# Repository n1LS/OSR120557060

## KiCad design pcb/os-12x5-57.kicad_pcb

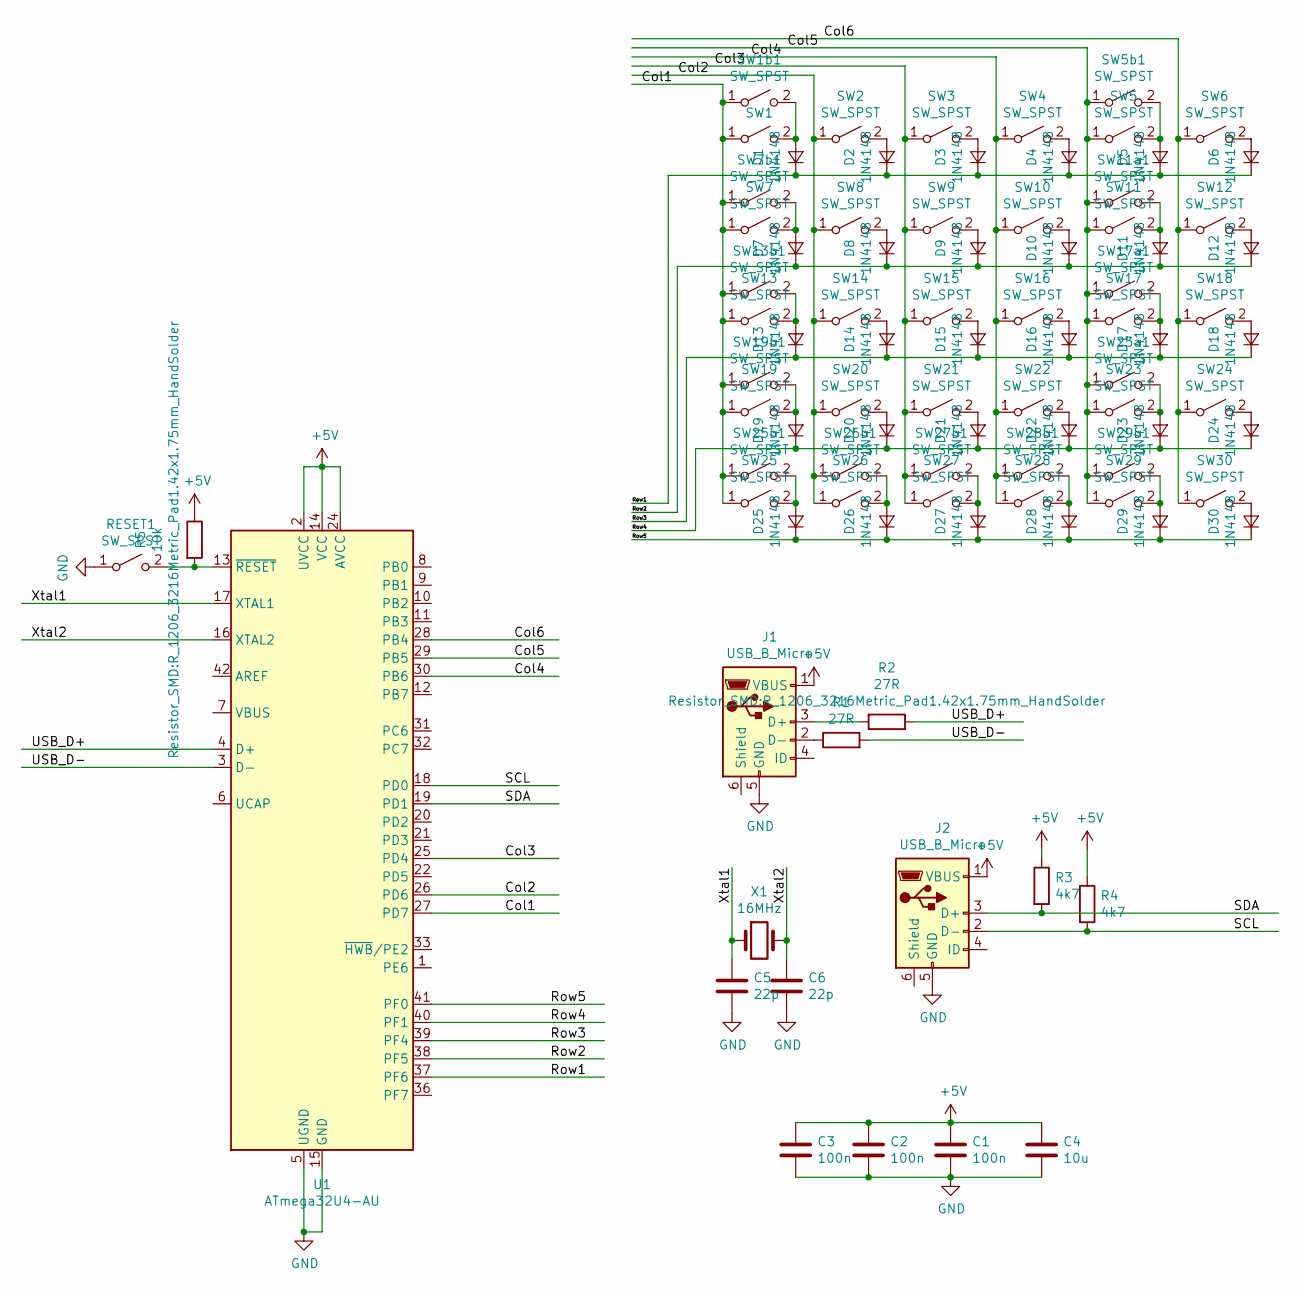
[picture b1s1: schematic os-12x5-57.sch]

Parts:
C1, C2, C3: 100n; C_1206_3216Metric_Pad1.42x1.75mm_HandSolder
C4: 10u; C_1206_3216Metric_Pad1.42x1.75mm_HandSolder
C5, C6: 22p; C_1206_3216Metric_Pad1.42x1.75mm_HandSolder
D1, D2, D3, D4, D5, D6, D7, D8, D9, D10, D11, D12, D13, D14, D15, D16, D17, D18, D19, D20, D21, D22, D23, D24, D25, D26, D27, D28, D29, D30: 1N4148; D_SOD-123
J1, J2: USB_B_Micro; USB_Micro-B_Molex_47346-0001
R1, R2: 27R; R_1206_3216Metric_Pad1.42x1.75mm_HandSolder
R3, R4: 4k7; R_1206_3216Metric_Pad1.42x1.75mm_HandSolder
R5: 10k; R_1206_3216Metric_Pad1.42x1.75mm_HandSolder
RESET1: SW_SPST; SW_SPST_B3U-1000P
SW1, SW1b1, SW2, SW3, SW4, SW5, SW5b1, SW6, SW7, SW7b1, SW8, SW9, SW10, SW11, SW11a1, SW12, SW13, SW13b1, SW14, SW15, SW16, SW17, SW17a1, SW18, SW19, SW19b1, SW20, SW21, SW22, SW23, SW23a1, SW24, SW25, SW25b1, SW26, SW26b1, SW27, SW27b1, SW28, SW28b1, SW29, SW29b1, SW30: SW_SPST; SW_Cherry_MX_1.00u_Plate
U1: ATmega32U4-AU; TQFP-44_10x10mm_P0.8mm
X1: 16MHz; Crystal_HC49-4H_Vertical

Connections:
+5V: C1.1, C2.1, C3.1, C4.1, J1.1 (VBUS), J2.1 (VBUS), R3.1, R4.1, R5.1, U1.2 (UVCC), U1.14 (VCC), U1.24 (AVCC), U1.34 (VCC), U1.44 (AVCC)
/Col1: SW1.1 (A), SW1b1.1 (A), SW7.1 (A), SW7b1.1 (A), SW13.1 (A), SW13b1.1 (A), SW19.1 (A), SW19b1.1 (A), SW25.1 (A), SW25b1.1 (A), U1.27 (PD7)
/Col2: SW2.1 (A), SW8.1 (A), SW14.1 (A), SW20.1 (A), SW26.1 (A), SW26b1.1 (A), U1.26 (PD6)
/Col3: SW3.1 (A), SW9.1 (A), SW15.1 (A), SW21.1 (A), SW27.1 (A), SW27b1.1 (A), U1.25 (PD4)
/Col4: SW4.1 (A), SW10.1 (A), SW16.1 (A), SW22.1 (A), SW28.1 (A), SW28b1.1 (A), U1.30 (PB6)
/Col5: SW5.1 (A), SW5b1.1 (A), SW11.1 (A), SW11a1.1 (A), SW17.1 (A), SW17a1.1 (A), SW23.1 (A), SW23a1.1 (A), SW29.1 (A), SW29b1.1 (A), U1.29 (PB5)
/Col6: SW6.1 (A), SW12.1 (A), SW18.1 (A), SW24.1 (A), SW30.1 (A), U1.28 (PB4)
/Row1: D1.1 (K), D2.1 (K), D3.1 (K), D4.1 (K), D5.1 (K), D6.1 (K), U1.37 (PF6)
/Row2: D7.1 (K), D8.1 (K), D9.1 (K), D10.1 (K), D11.1 (K), D12.1 (K), U1.38 (PF5)
/Row3: D13.1 (K), D14.1 (K), D15.1 (K), D16.1 (K), D17.1 (K), D18.1 (K), U1.39 (PF4)
/Row4: D19.1 (K), D20.1 (K), D21.1 (K), D22.1 (K), D23.1 (K), D24.1 (K), U1.40 (PF1)
/Row5: D25.1 (K), D26.1 (K), D27.1 (K), D28.1 (K), D29.1 (K), D30.1 (K), U1.41 (PF0)
/SCL: J2.2 (D-), R4.2, U1.18 (PD0)
/SDA: J2.3 (D+), R3.2, U1.19 (PD1)
/USB_D+: R2.1, U1.4 (D+)
/USB_D-: R1.2, U1.3 (D-)
/Xtal1: C5.1, U1.17 (XTAL1), X1.1
/Xtal2: C6.1, U1.16 (XTAL2), X1.2
GND: C1.2, C2.2, C3.2, C4.2, C5.2, C6.2, J1.5 (GND), J2.5 (GND), RESET1.1 (A), U1.5 (UGND), U1.15 (GND), U1.23 (GND), U1.35 (GND), U1.43 (GND)
unnamed: D1.2 (A), SW1.2 (B), SW1b1.2 (B)
unnamed: D2.2 (A), SW2.2 (B)
unnamed: D3.2 (A), SW3.2 (B)
unnamed: D4.2 (A), SW4.2 (B)
unnamed: D5.2 (A), SW5.2 (B), SW5b1.2 (B)
unnamed: D6.2 (A), SW6.2 (B)
unnamed: D7.2 (A), SW7.2 (B), SW7b1.2 (B)
unnamed: D8.2 (A), SW8.2 (B)
unnamed: D9.2 (A), SW9.2 (B)
unnamed: D10.2 (A), SW10.2 (B)
unnamed: D11.2 (A), SW11.2 (B), SW11a1.2 (B)
unnamed: D12.2 (A), SW12.2 (B)
unnamed: D13.2 (A), SW13.2 (B), SW13b1.2 (B)
unnamed: D14.2 (A), SW14.2 (B)
unnamed: D15.2 (A), SW15.2 (B)
unnamed: D16.2 (A), SW16.2 (B)
unnamed: D17.2 (A), SW17.2 (B), SW17a1.2 (B)
unnamed: D18.2 (A), SW18.2 (B)
unnamed: D19.2 (A), SW19.2 (B), SW19b1.2 (B)
unnamed: D20.2 (A), SW20.2 (B)
unnamed: D21.2 (A), SW21.2 (B)
unnamed: D22.2 (A), SW22.2 (B)
unnamed: D23.2 (A), SW23.2 (B), SW23a1.2 (B)
unnamed: D24.2 (A), SW24.2 (B)
unnamed: D25.2 (A), SW25.2 (B), SW25b1.2 (B)
unnamed: D26.2 (A), SW26.2 (B), SW26b1.2 (B)
unnamed: D27.2 (A), SW27.2 (B), SW27b1.2 (B)
unnamed: D28.2 (A), SW28.2 (B), SW28b1.2 (B)
unnamed: D29.2 (A), SW29.2 (B), SW29b1.2 (B)
unnamed: D30.2 (A), SW30.2 (B)
unnamed: J1.2 (D-), R1.1
unnamed: J1.3 (D+), R2.2
unnamed: R5.2, RESET1.2 (B), U1.13 (~RESET)

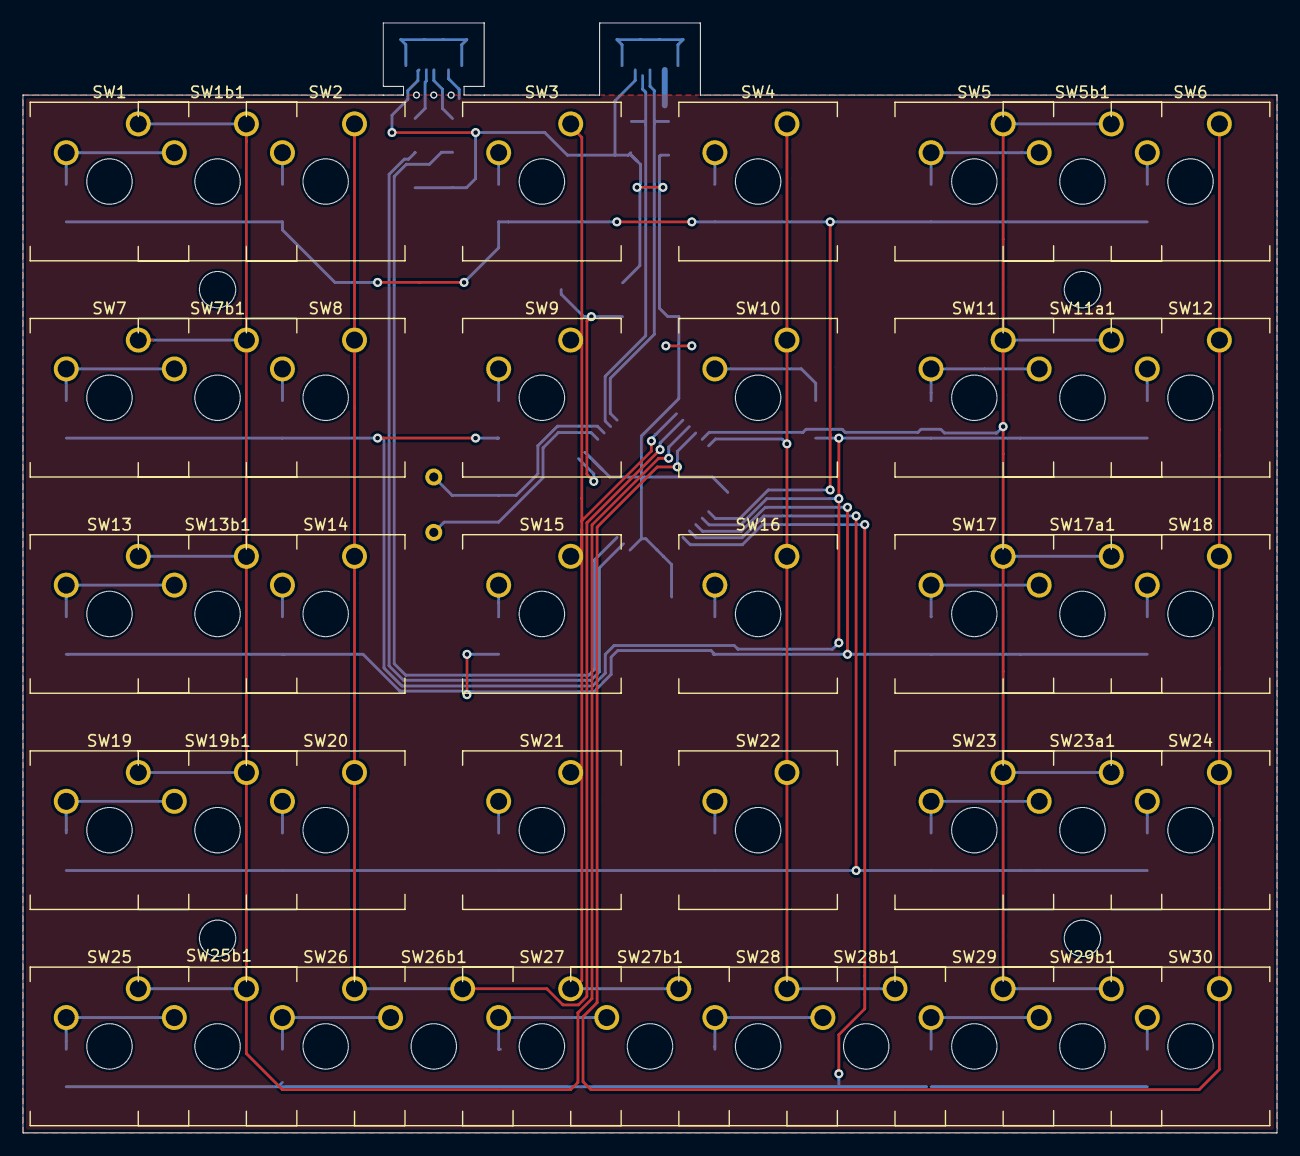
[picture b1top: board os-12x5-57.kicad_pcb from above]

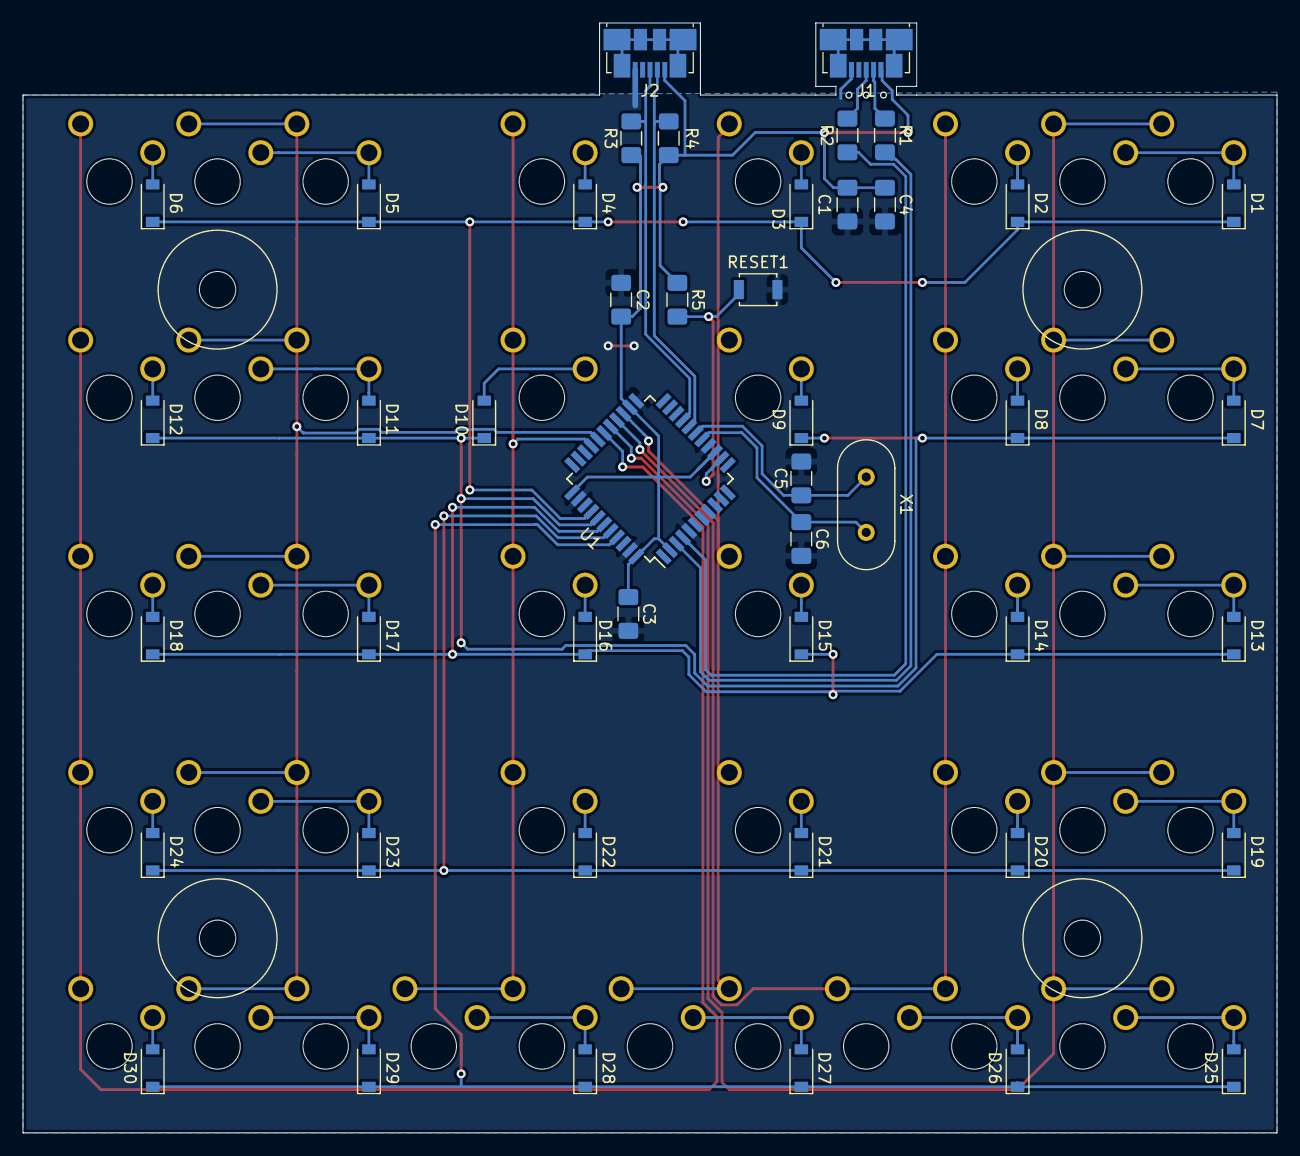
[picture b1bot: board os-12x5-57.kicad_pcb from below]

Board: 2 copper layers, 110.5 x 97.8 mm, 89 parts (46 on the bottom side), 52 nets.
